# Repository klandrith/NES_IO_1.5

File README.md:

NES-I/O 1.5
===========

From original Borti's project: https://github.com/borti4938/NES_IGR_for_NESRGB/tree/master/NES-IO

an idea by Arcade-TV from circuit-board.de :) Thank you very much!!!

The board replaces the silver box in NES frontloader. On this PCB the following components are included:

- AC input jack
- AC to DC conversion
- MultiAV (SNES and GC(*) are supported) 
- PIC16F684 microcontroller to control the NESRGB color palette and reset the console using your controller :D

All components you need are stated on the silkscreen. An complete overview as well as an English installation guide is coming soon ;)

Grab the firmware for the PIC16F684 here: https://github.com/borti4938/NES_IGR_for_NESRGB/tree/master/fw/IGR_for_NESRGB/
- current version: use the 'normal version' and flash the nesrgb_igr_684_var_led.hex
- oldest PCB version (with three 10k resistors next to the 74*125): use the 'risky version' and flash nesrgb_igr_684_risky_var_led.hex

(*) 3d-printed Helder/Buffalowing connector on assemblergames (http://assemblergames.com/l/threads/f-s-nes-top-loader-snes-style-multi-a-v-socket.50494/) also fits  
    thanks for figuring out, splits (shmups forum)

-- The Rev 1.5 add the audio module, and there is now a NO CUT version where a miniDIN 9pin and a miniDIN 4pin replace the SNES/GC Multiout.
--
-- YOU'LL NEED TO REMOVE THE 3 RESISTORS ON THE RGB LINES OF THE NESRGB BOARD IF YOU ARE USING THE NOCUT BOARDS
--

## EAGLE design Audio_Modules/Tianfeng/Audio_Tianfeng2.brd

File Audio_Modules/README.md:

NES-I/O 1.5
===========

This is the Audio Module folder.

You'll find audio that can replace the blank one on the NES I/O / Famicom I/O Rev 1.5

* Tianfeng audio - This will take directly from the CPU Pin 1/2 and expansion cart pin.

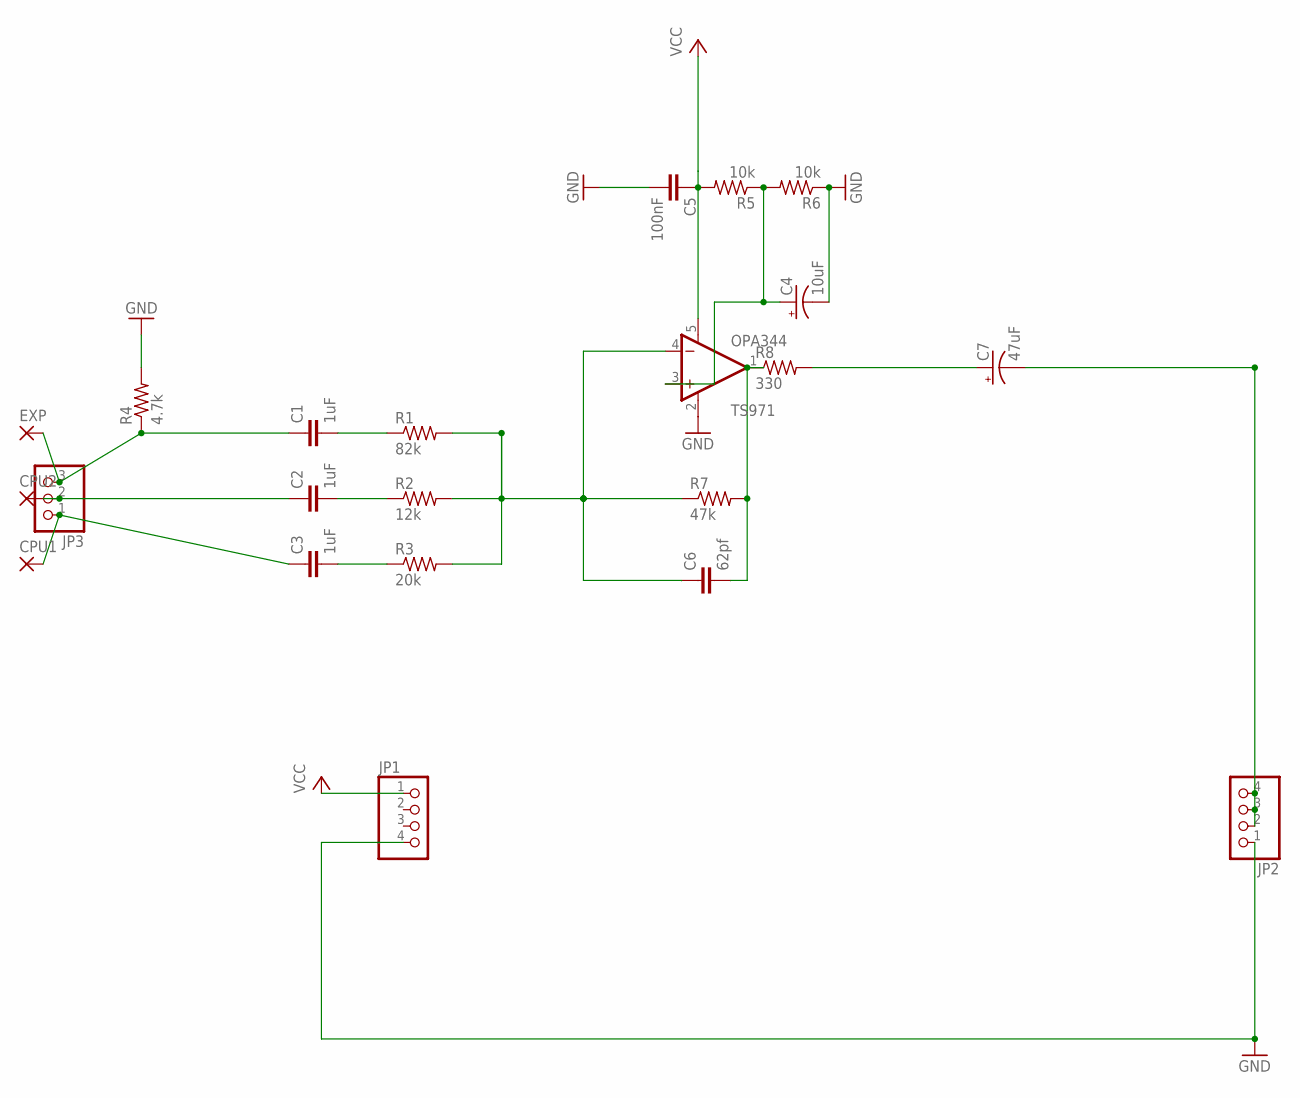
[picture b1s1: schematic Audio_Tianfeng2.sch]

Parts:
C1, C2, C3: 1uF; C0603K
C4: 10uF; 153CLV-0405
C5: 100nF; C0603K
C6: 62pf; C0603K
C7: 47uF; 153CLV-0405
CPU1, CPU2: SMD2; SMD1,27-2,54
EXP: SMD2; SMD1,27-2,54
JP1, JP2: PINHD-1X04_2.54-S; 1X04-S
JP3: PINHD-1X03_2.54-S; 1X03-S
R1: 82k; R0603
R2: 12k; R0603
R3: 20k; R0603
R4: 4.7k; R0603
R5, R6: 10k; R0603
R7: 47k; R0603
R8: 330; R0603
TS971: OPA344; SOT23-5

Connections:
GND: C4.-, C5.2, JP1.4, JP2.1, R4.2, R6.1, TS971.2 (V-)
unnamed: C1.2, R1.1
unnamed: C2.2, R2.1
unnamed: C4.+, R5.1, R6.2, TS971.3 (+IN)
unnamed: C7.-, JP2.2, JP2.3, JP2.4
unnamed: C3.2, R3.1
unnamed: C6.1, R1.2, R2.2, R3.2, R7.1, TS971.4 (-IN)
unnamed: C1.1, EXP.1, JP3.3, R4.1
unnamed: C2.1, CPU2.1, JP3.2
unnamed: C3.1, CPU1.1, JP3.1
unnamed: C6.2, R7.2, R8.1, TS971.1 (OUT)
unnamed: C7.+, R8.2
VCC: C5.1, JP1.1, R5.2, TS971.5 (V+)

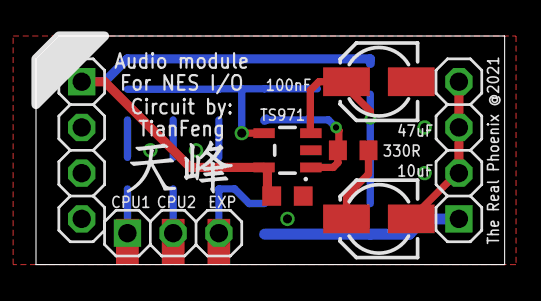
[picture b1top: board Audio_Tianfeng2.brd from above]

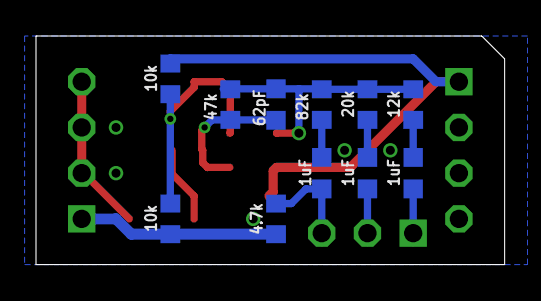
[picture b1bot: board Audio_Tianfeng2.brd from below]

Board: 2 copper layers, 26.0 x 12.7 mm, 22 parts (11 on the bottom side), 13 nets.

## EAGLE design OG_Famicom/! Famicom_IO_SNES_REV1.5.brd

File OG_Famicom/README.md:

Famicom-I/O 1.5
===========

This is the Original Famicom folder.

The Classic SNES Multiout requires the following PCBs (gerber zipped files):
- Famicom_IO_SNES_REV1.5
- Audio_Blank
- Famicon_IO_Jack_Spacer

The NOCUT requires the following PCBs (gerber zipped files):
- Famicom_IO_NOCUT_REV1.5
- Audio_Blank
- Famicon_IO_Jack_Spacer

Installation Notes:
- For the NOCUT version, you need to remove the 75omhs resistors on the RGB lines of the NESRGB

- PDF installation guide link: https://github.com/TRP-Retromods/NES_IO_1.5/blob/master/OG_Famicom/Famicom_IO_Installation.pdf

Audio
- For default installation, you have 3 possibilies

1) No expansion: you simply take CPU pins 1&2 to A&B inputs of the NESRGB, then link O ouput to "Mono" of the Famicom I/O
2) Expansion only: you need to CUT the trace going to pin 45 of the Cart slot (as per Tim's installation guide). As Tim said: "connect the A and B inputs to the PPU, connect the cartridge output pin via a resistor to the mixing point (located next to jumper J5). The cartridge input pin needs to be disconnected from the existing mixer circuit on the motherboard. Replace it with a mid supply reference (maybe 4k7 to +5V, 4k7 to ground, bypassed with a 10u capacitor)"
3) Original mixing (TO BE TESTED) : quote "Alternatively, you can continue to use the original mixer circuit and just use the NESRGB audio circuit as a buffer. To do this connect the cartridge output through a 27k resistor to the A audio input on the NESRGB board. Leave the B audio input unconnected. This makes the audio circuit into unity gain buffer. You will also probably want to remove C30 as it will attenuate the high frequency signals too much in this configuration."

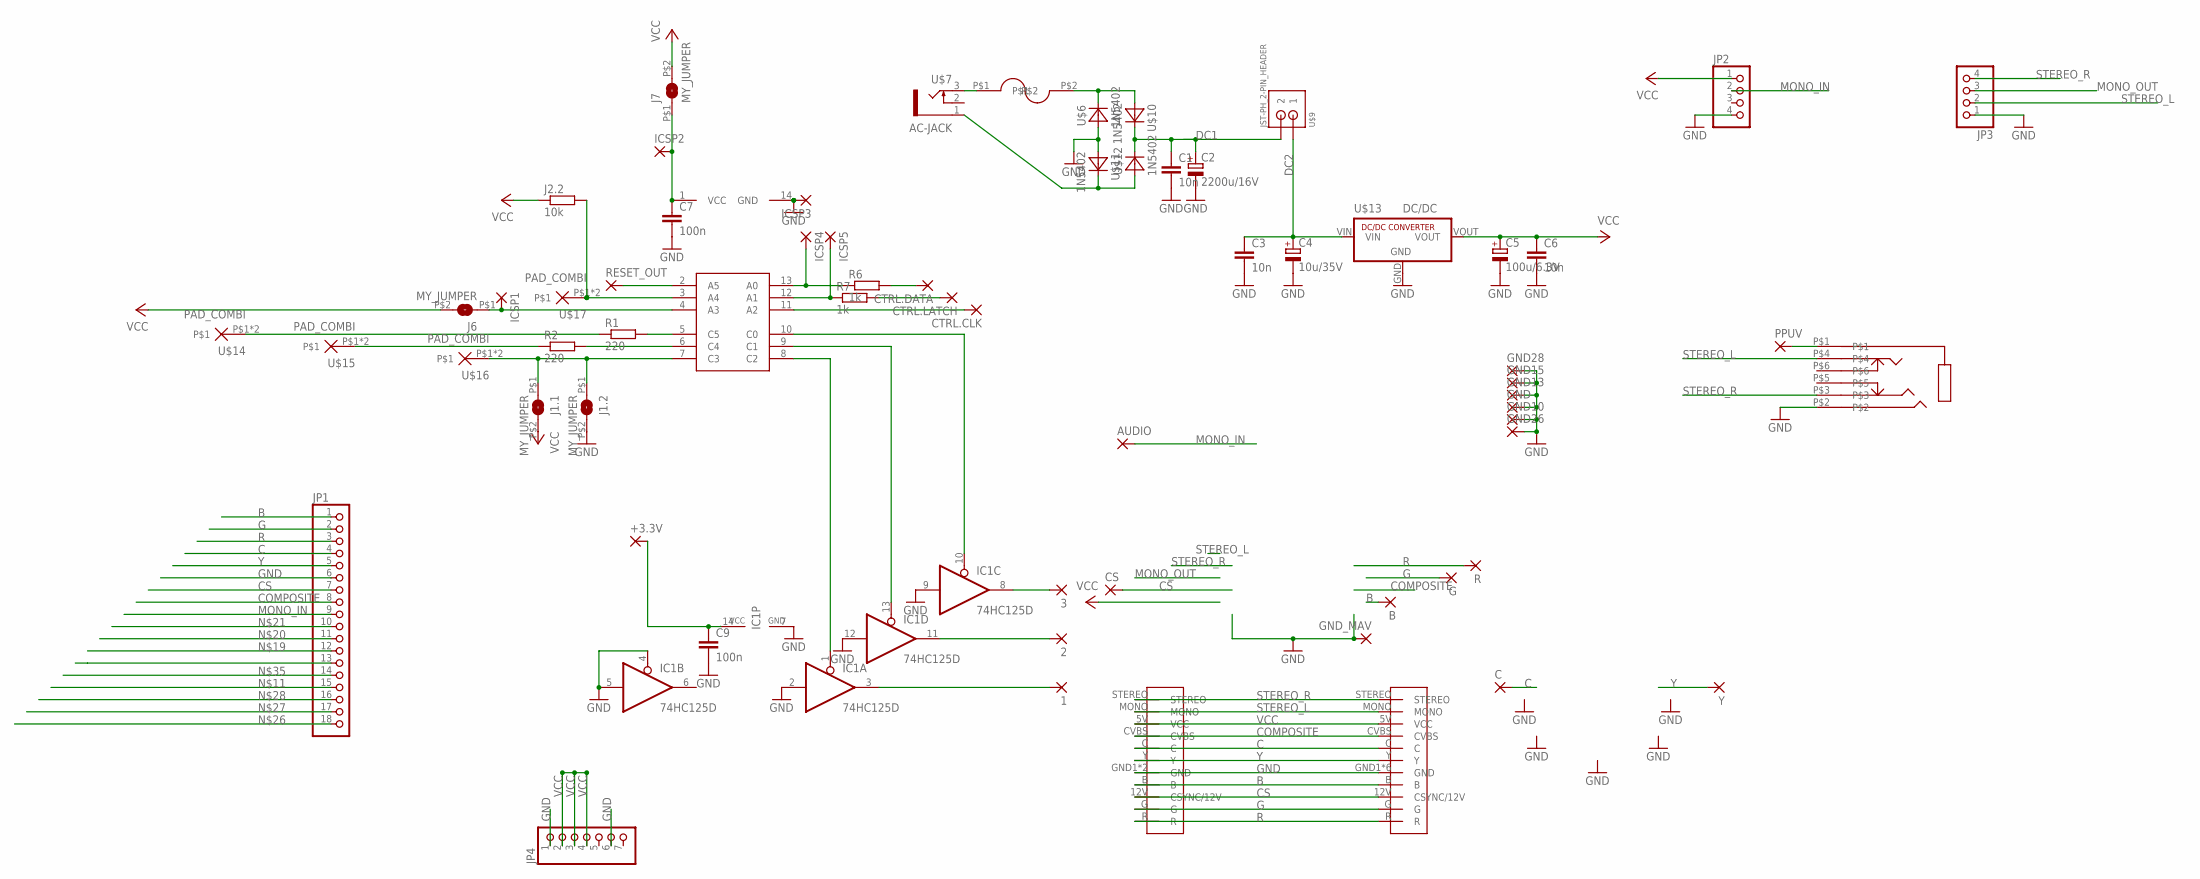
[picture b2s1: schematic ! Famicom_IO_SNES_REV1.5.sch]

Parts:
1, 2, 3: SMD2; SMD1,27-2,54
+3.3V: SMD2; SMD1,27-2,54
AUDIO: SMD2; SMD1,27-2,54
B: SMD2; SMD1,27-2,54
C: SMD2; SMD1,27-2,54
C1, C3, C6: 10n; Z0805
C2: 2200u/16V; E5-13
C4: 10u/35V; PANASONIC_B
C5: 100u/6.3V; PANASONIC_D
C7, C9: 100n; Z0805
CS: SMD2; SMD1,27-2,54
CTRL.CLK, CTRL.DATA, CTRL.LATCH: SMD2; SMD1,27-2,54
G: SMD2; SMD1,27-2,54
GND, GND10, GND13, GND15, GND26, GND28: SMD5; SMD2,54-5,08
GND_MAV: SMD2; SMD1,27-2,54
IC1: 74HC125D; SO14
ICSP1, ICSP2, ICSP3, ICSP4, ICSP5: 1,6/0,8
J1.1, J1.2, J6, J7: MY_JUMPER; MYJUMP
J2.2: 10k; Z0805
JP1: PINHD-1X18_2.00; 1X18M
JP2, JP3: PINHD-1X04_2.54-S; 1X04-S
JP4: PINHD-1X07_2.54-S; 1X07-S
PPUV: SMD2; SMD1,27-2,54
R: SMD2; SMD1,27-2,54
R1, R2: 220; Z0805
R6, R7: 1k; Z0805
RESET_OUT: SMD2; SMD1,27-2,54
U$2: FUSEHOLDER
U$5: PIC16F630_SIMPLE; PIC16F630
U$6, U$10, U$11, U$12: 1N5402; DO201
U$7: AC-JACK
U$8: PJ-342D; PJ-342
U$9: JST-PH_2-PIN_HEADER; JST_B2B-PH_HEADER
U$13: DC/DC; RECOM
U$14, U$15, U$16, U$17: PAD_COMBI
U$19: GC-MULTIAV
U$20: SNES-MULTIAV2
Y: SMD2; SMD1,27-2,54

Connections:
AC1A: U$2.P$1, U$7.3
AC1B: U$2.P$2, U$6.C, U$10.A
AC2: U$7.1 (5), U$11.C, U$12.A
B: B.1, JP1.1, U$19.B, U$20.B
C: C.1, JP1.4, U$19.C, U$20.C
COMPOSITE: JP1.8, PPUV.1, U$8.P$1, U$19.CVBS, U$20.CVBS
CS: CS.1, JP1.7, U$19.12V (CSYNC/12V), U$20.12V (CSYNC/12V)
DC1: C1.1, C2.+, U$9.P2 (2), U$10.C, U$12.C
DC2: C3.1, C4.+, U$9.P1 (1), U$13.VIN
G: G.1, JP1.2, U$19.G, U$20.G
GND: C1.2, C2.-, C3.2, C4.-, C5.-, C6.2, C7.2, C9.2, GND.1, GND10.1, GND13.1, GND15.1, GND26.1, GND28.1, GND_MAV.1, IC1.2 (I), IC1.4 (OE), IC1.5 (I), IC1.7 (GND), IC1.9 (I), IC1.12 (I), ICSP3.1, J1.2.P$2 (2), JP1.6, JP2.4, JP3.1, JP4.1, JP4.6, U$5.14 (GND), U$6.A, U$8.P$2, U$11.A, U$13.GND, U$19.GND1 (GND), U$19.GND2 (GND), U$19.GND3 (GND), U$19.GND4 (GND), U$19.GND5 (GND), U$19.GND6 (GND), U$20.GND1 (GND), U$20.GND2 (GND)
MONO_IN: AUDIO.1, JP1.9, JP2.2
MONO_OUT: JP3.3
unnamed: 3.1, IC1.8 (O), JP1.15
unnamed: J2.2.2, U$5.3 (A4), U$17.P$1, U$17.P$2
unnamed: R1.2, U$5.5 (C5)
unnamed: R2.2, U$5.6 (C4)
unnamed: R1.1, U$14.P$1, U$14.P$2
unnamed: R2.1, U$15.P$1, U$15.P$2
unnamed: J1.1.P$1 (1), J1.2.P$1 (1), U$5.7 (C3), U$16.P$1, U$16.P$2
unnamed: CTRL.DATA.1, JP1.12, R6.2
unnamed: CTRL.LATCH.1, JP1.11, R7.2
unnamed: CTRL.CLK.1, JP1.10, U$5.11 (A2)
unnamed: IC1.10 (OE), U$5.10 (C0)
unnamed: IC1.13 (OE), U$5.9 (C1)
unnamed: IC1.1 (OE), U$5.8 (C2)
unnamed: +3.3V.1, C9.1, IC1.14 (VCC), JP1.18
unnamed: 1.1, IC1.3 (O), JP1.17
unnamed: 2.1, IC1.11 (O), JP1.16
unnamed: C7.1, ICSP2.1, J7.P$1 (1), U$5.1 (VCC)
unnamed: ICSP1.1, J6.P$1 (1), U$5.4 (A3)
unnamed: ICSP4.1, R6.1, U$5.13 (A0)
unnamed: ICSP5.1, R7.1, U$5.12 (A1)
unnamed: JP1.14, RESET_OUT.1, U$5.2 (A5)
R: JP1.3, R.1, U$19.R, U$20.R
STEREO_L: JP3.2, U$8.P$4, U$19.MONO, U$20.MONO
STEREO_R: JP3.4, U$8.P$3, U$19.STEREO, U$20.STEREO
VCC: C5.+, C6.1, J1.1.P$2 (2), J2.2.1, J6.P$2 (2), J7.P$2 (2), JP2.1, JP4.2, JP4.3, JP4.4, U$13.VOUT, U$19.5V (VCC), U$20.5V (VCC)
Y: JP1.5, U$19.Y, U$20.Y, Y.1

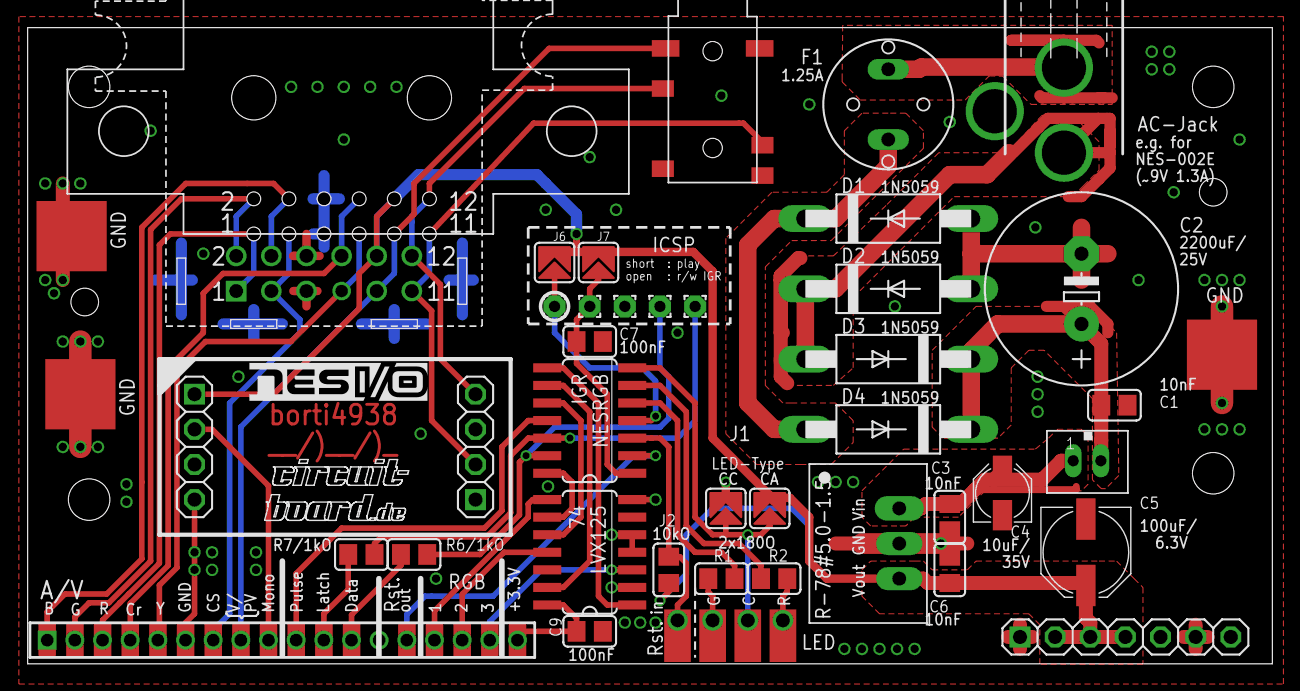
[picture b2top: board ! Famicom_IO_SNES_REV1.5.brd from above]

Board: 2 copper layers, 90.0 x 46.0 mm, 68 parts (1 on the bottom side), 38 nets.

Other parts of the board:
U$3, U$4: NESIO-LOGO

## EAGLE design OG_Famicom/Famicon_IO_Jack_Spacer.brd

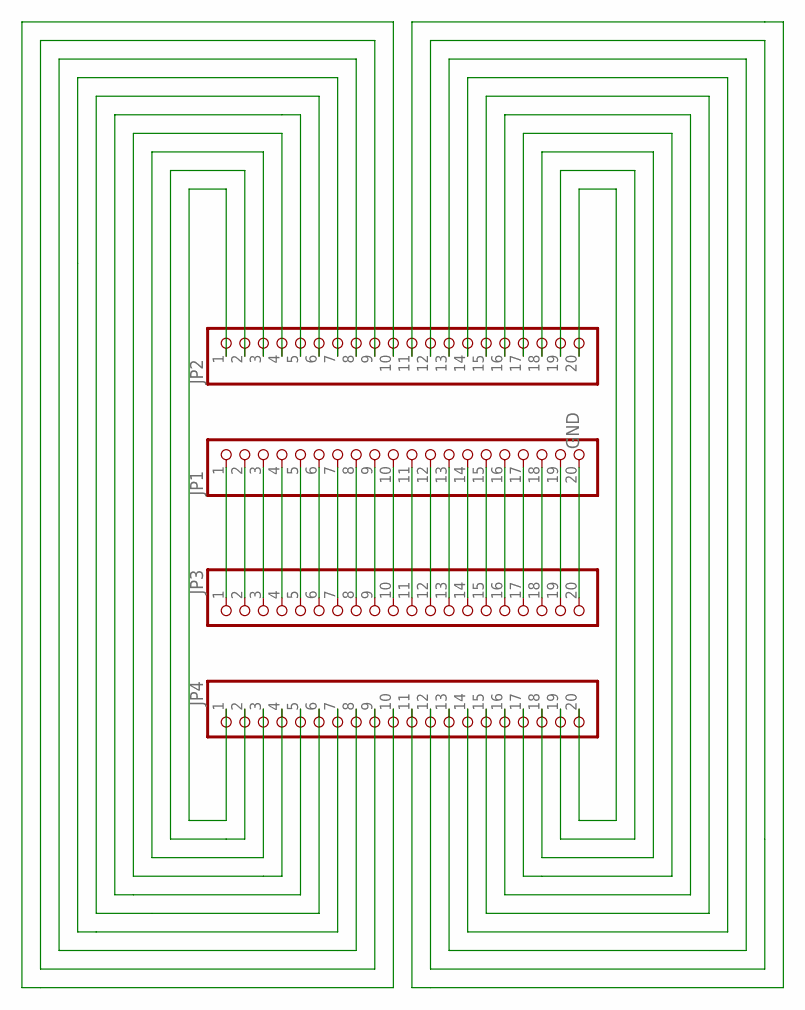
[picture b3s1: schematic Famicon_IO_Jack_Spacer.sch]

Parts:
JP1, JP2, JP3, JP4: PINHD-1X20_2.54-S; 1X20-S

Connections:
GND: JP1.20, JP3.20
unnamed: JP1.1, JP3.1
unnamed: JP1.2, JP3.2
unnamed: JP1.3, JP3.3
unnamed: JP1.4, JP3.4
unnamed: JP1.5, JP3.5
unnamed: JP1.6, JP3.6
unnamed: JP1.7, JP3.7
unnamed: JP1.8, JP3.8
unnamed: JP1.9, JP3.9
unnamed: JP1.10, JP3.10
unnamed: JP1.11, JP3.11
unnamed: JP1.12, JP3.12
unnamed: JP1.13, JP3.13
unnamed: JP1.14, JP3.14
unnamed: JP1.15, JP3.15
unnamed: JP1.16, JP3.16
unnamed: JP1.17, JP3.17
unnamed: JP1.18, JP3.18
unnamed: JP1.19, JP3.19
unnamed: JP2.20, JP4.20
unnamed: JP2.19, JP4.19
unnamed: JP2.18, JP4.18
unnamed: JP2.17, JP4.17
unnamed: JP2.16, JP4.16
unnamed: JP2.15, JP4.15
unnamed: JP2.1, JP4.1
unnamed: JP2.2, JP4.2
unnamed: JP2.3, JP4.3
unnamed: JP2.4, JP4.4
unnamed: JP2.5, JP4.5
unnamed: JP2.6, JP4.6
unnamed: JP2.14, JP4.14
unnamed: JP2.7, JP4.7
unnamed: JP2.13, JP4.13
unnamed: JP2.12, JP4.12
unnamed: JP2.8, JP4.8
unnamed: JP2.9, JP4.9
unnamed: JP2.11, JP4.11
unnamed: JP2.10, JP4.10

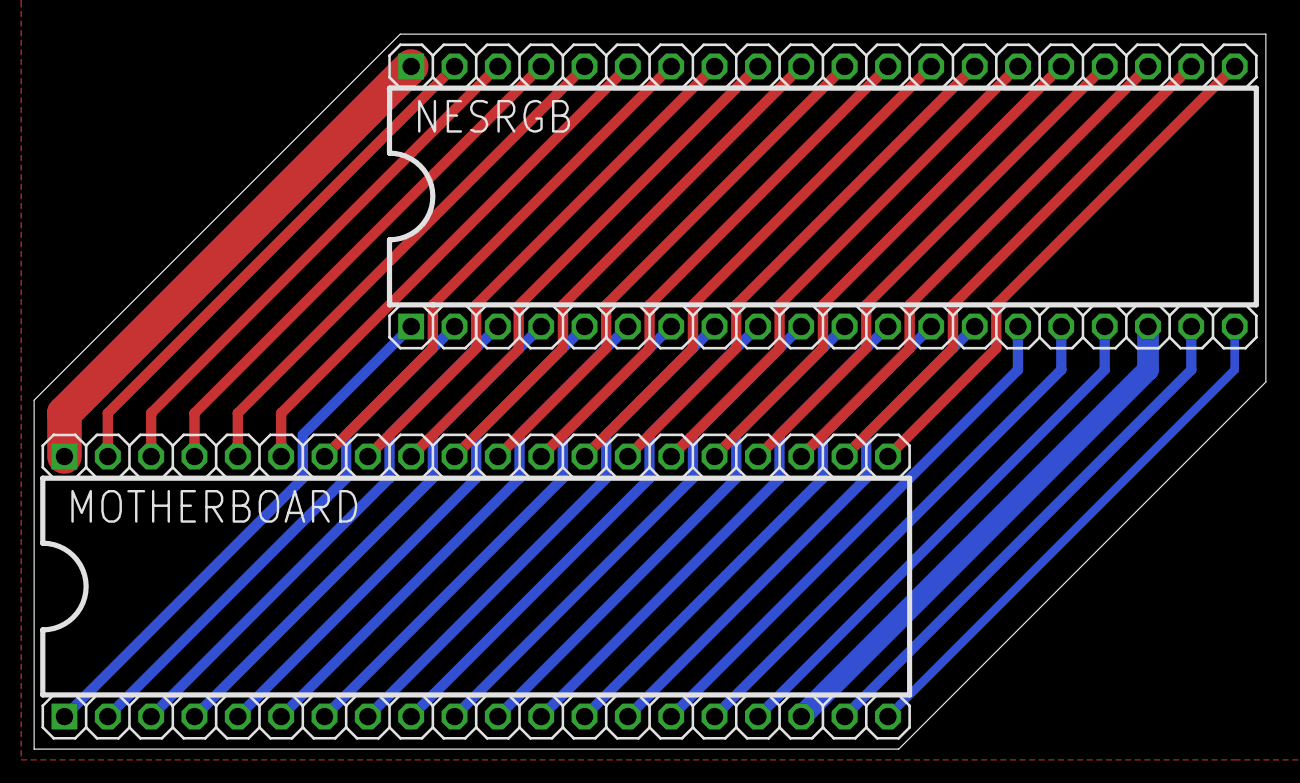
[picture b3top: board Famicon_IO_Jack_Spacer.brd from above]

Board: 2 copper layers, 72.2 x 41.9 mm, 4 parts (0 on the bottom side), 40 nets.

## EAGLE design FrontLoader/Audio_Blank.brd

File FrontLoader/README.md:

NES-I/O 1.5
===========

This is the FrontLoader folder.

The Classic SNES Multiout requires the following PCBs (gerber zipped files):
- NES_IO_US_REV1.5_SNES
- Audio_Blank

The NOCUT requires the following PCBs (gerber zipped files):
- NES_IO_US_REV1.5_NOCUT
- miniDIN4_spacer
- Audio_Blank

-- You need to send to fab the blank audio module PCB for all versions, and the miniDIN 4 spacer IN 1MM THICK for the NOCUT.
--
-- You'll need to cut some parts on the PCBs: they are currently designed to avoid extra costs on castelated vias.
--
-- They are around the RCA plugs and on the miniDIN4_spacer.
--

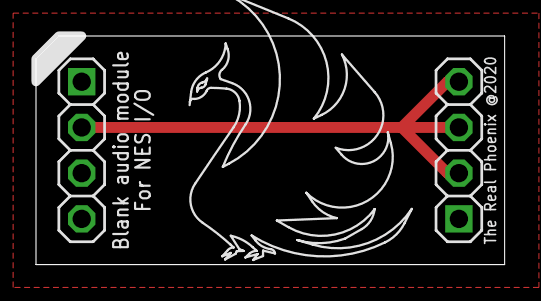
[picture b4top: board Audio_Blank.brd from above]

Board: 2 copper layers, 26.0 x 12.7 mm, 3 parts (0 on the bottom side), 2 nets.

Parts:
JP1, JP2: 1X04-S
U$1: LOGO

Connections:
GND: JP1.4, JP2.1
unnamed: JP1.2, JP2.2, JP2.3, JP2.4

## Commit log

2020-12-10 Reorgize a bit
    Reorgize a bit
2020-12-23 Create Borti_NESIO_1-5_NOCUT_BOM.xlsx
    Add BOM file for the NoCut.
    The MultiOUT is the same but ignore both miniDINs
2021-02-18 Add Eagle files
    Add Eagle files
2021-04-28 Famicom I/O
    - Push Famicom I/O
    - Cleaning, Sorting
    - Add audio Tianfeng audio module
2021-07-20 Add installation guide in PDF to Famicom I/O

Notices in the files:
parts and their libraries:
SparkFun-AnalogIC: Licensing:Creative Commons ShareAlike 4.0 International - https://creativecommons.org/licenses/by-sa/4.0
